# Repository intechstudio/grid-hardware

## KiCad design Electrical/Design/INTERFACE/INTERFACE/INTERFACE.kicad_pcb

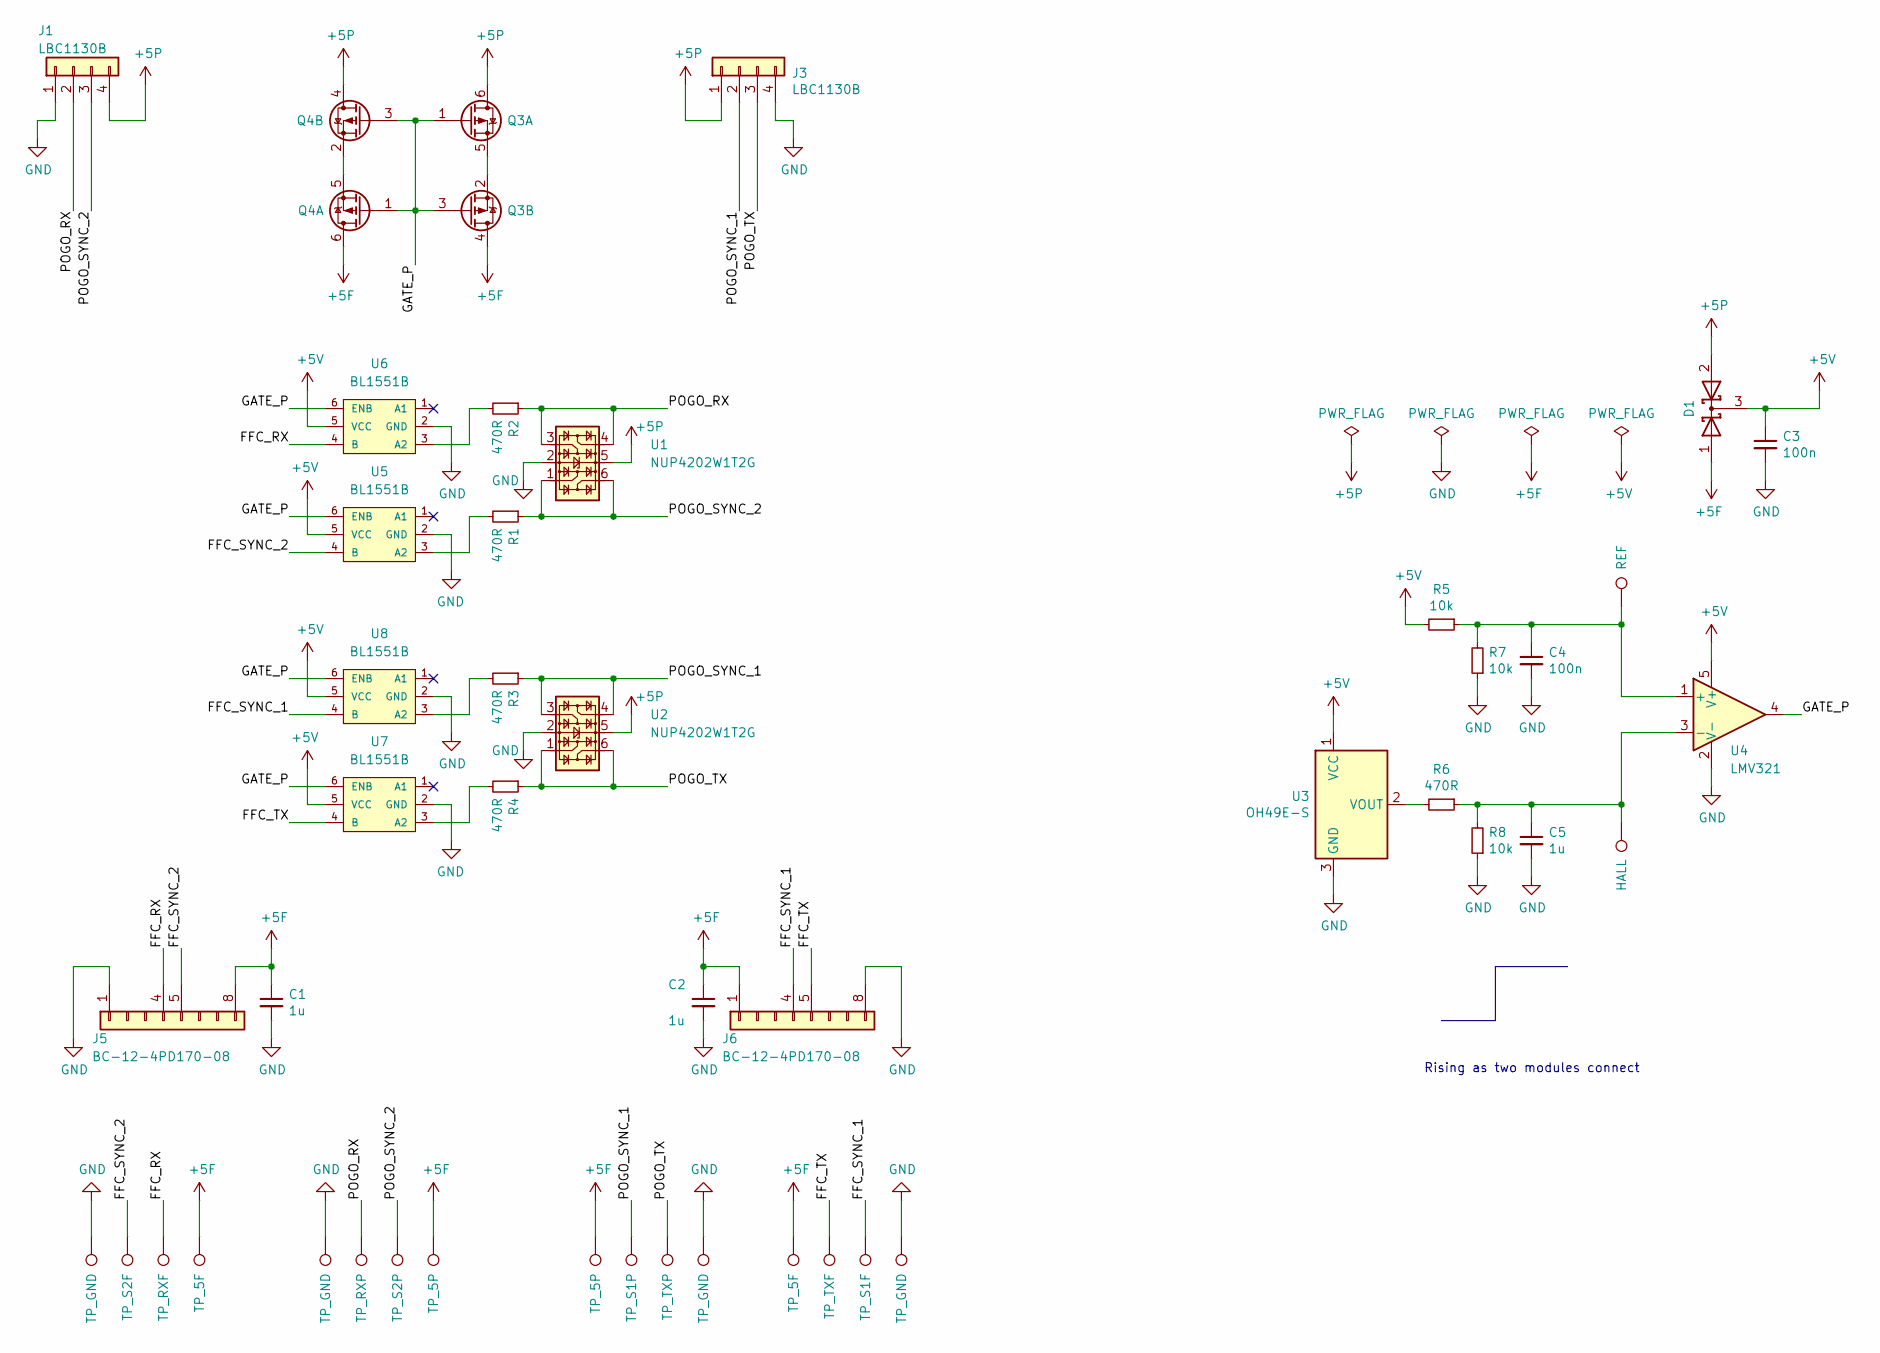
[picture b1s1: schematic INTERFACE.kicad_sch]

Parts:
C1, C2, C5: 1u; CAP_0805
C3, C4: 100n; CAP_0805
D1: BAT54C; SOT-23; Part C375703
J1, J3: LBC1130B; J_4xPOGO_SMD; Part LBC1130B
J5, J6: BC-12-4PD170-08; J_BATTERY_CONN
Q3, Q4: WST2011; SOT-23-6; Part C148368
R1, R2, R3, R4, R6: 470R; RES_0402
R5, R7, R8: 10k; RES_0805
TP1, TP8, TP9, TP16: TP_GND; TestPoint_THTPad_1.0x1.0mm_Drill0.5mm
TP2: TP_S2F; TestPoint_THTPad_1.0x1.0mm_Drill0.5mm
TP3: TP_RXF; TestPoint_THTPad_1.0x1.0mm_Drill0.5mm
TP4, TP5: TP_5F; TestPoint_THTPad_1.0x1.0mm_Drill0.5mm
TP6: TP_TXF; TestPoint_THTPad_1.0x1.0mm_Drill0.5mm
TP7: TP_S1F; TestPoint_THTPad_1.0x1.0mm_Drill0.5mm
TP10: TP_RXP; TestPoint_THTPad_1.0x1.0mm_Drill0.5mm
TP11: TP_S2P; TestPoint_THTPad_1.0x1.0mm_Drill0.5mm
TP12, TP13: TP_5P; TestPoint_THTPad_1.0x1.0mm_Drill0.5mm
TP14: TP_S1P; TestPoint_THTPad_1.0x1.0mm_Drill0.5mm
TP15: TP_TXP; TestPoint_THTPad_1.0x1.0mm_Drill0.5mm
TP17: REF; TestPoint_THTPad_1.0x1.0mm_Drill0.5mm
TP18: HALL; TestPoint_THTPad_1.0x1.0mm_Drill0.5mm
U1, U2: NUP4202W1T2G; SOT-363_SC-70-6; Part C294963
U3: OH49E-S; SOT-23W; Part C85573
U4: LMV321; SOT-23-5; Part C90297
U5, U6, U7, U8: BL1551B; SOT-363_SC-70-6

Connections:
+5F: C1.1, C2.1, D1.1 (A), J5.8, J6.1, Q3.4 (D), Q4.6 (D), TP4.1, TP5.1, TP12.1, TP13.1
+5P: D1.2 (A), J1.4, J3.1, Q3.6 (D), Q4.4 (D), U1.5, U2.5
+5V: C3.1, D1.3 (K), R5.2, U3.1 (VCC), U4.5 (V+), U5.5 (VCC), U6.5 (VCC), U7.5 (VCC), U8.5 (VCC)
/FFC_RX: J5.4, TP3.1, U6.4 (B)
/FFC_SYNC_1: J6.4, TP7.1, U8.4 (B)
/FFC_SYNC_2: J5.5, TP2.1, U5.4 (B)
/FFC_TX: J6.5, TP6.1, U7.4 (B)
/GATE_P: Q3.1 (G), Q3.3 (G), Q4.1 (G), Q4.3 (G), U4.4, U5.6 (ENB), U6.6 (ENB), U7.6 (ENB), U8.6 (ENB)
/POGO_RX: J1.2, R2.1, TP10.1, U1.3, U1.4
/POGO_SYNC_1: J3.2, R3.1, TP14.1, U2.3, U2.4
/POGO_SYNC_2: J1.3, R1.1, TP11.1, U1.1, U1.6
/POGO_TX: J3.3, R4.1, TP15.1, U2.1, U2.6
GND: C1.2, C2.2, C3.2, C4.2, C5.2, J1.1, J3.4, J5.1, J6.8, R7.1, R8.1, TP1.1, TP8.1, TP9.1, TP16.1, U1.2, U2.2, U3.3 (GND), U4.2 (V-), U5.2 (GND), U6.2 (GND), U7.2 (GND), U8.2 (GND)
unnamed: Q3.2 (S), Q3.5 (S)
unnamed: Q4.2 (S), Q4.5 (S)
unnamed: R6.2, U3.2 (VOUT)
unnamed: C4.1, R5.1, R7.2, TP17.1, U4.1 (+)
unnamed: C5.1, R6.1, R8.2, TP18.1, U4.3 (-)
unnamed: R1.2, U5.3 (A2)
unnamed: R2.2, U6.3 (A2)
unnamed: R4.2, U7.3 (A2)
unnamed: R3.2, U8.3 (A2)

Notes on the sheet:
Rising as two modules connect

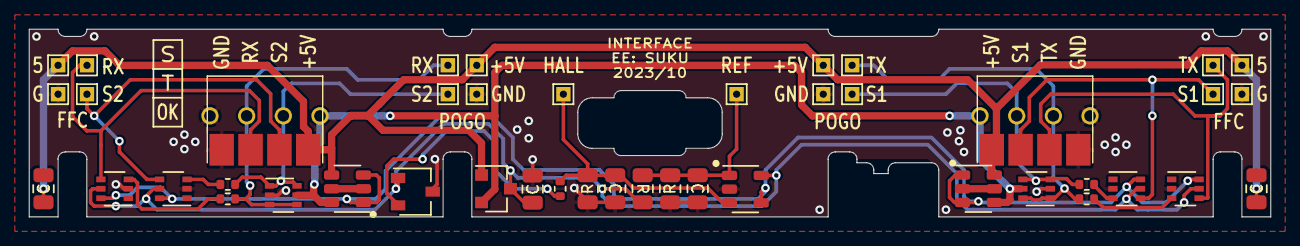
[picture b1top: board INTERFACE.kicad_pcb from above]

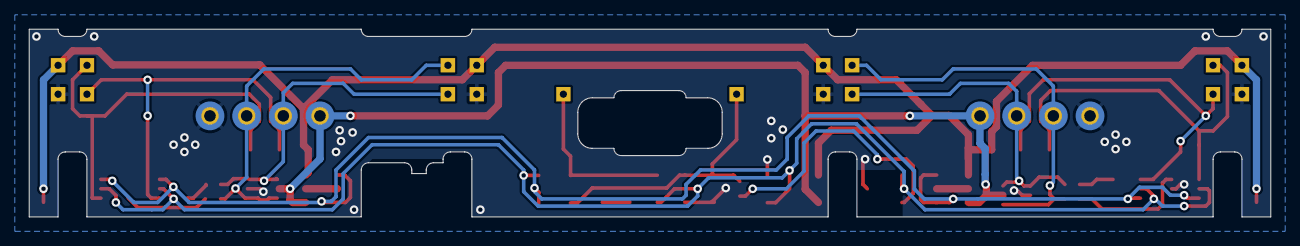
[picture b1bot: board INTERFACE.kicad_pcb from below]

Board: 2 copper layers, 86.0 x 13.0 mm, 46 parts (2 on the bottom side), 22 nets.

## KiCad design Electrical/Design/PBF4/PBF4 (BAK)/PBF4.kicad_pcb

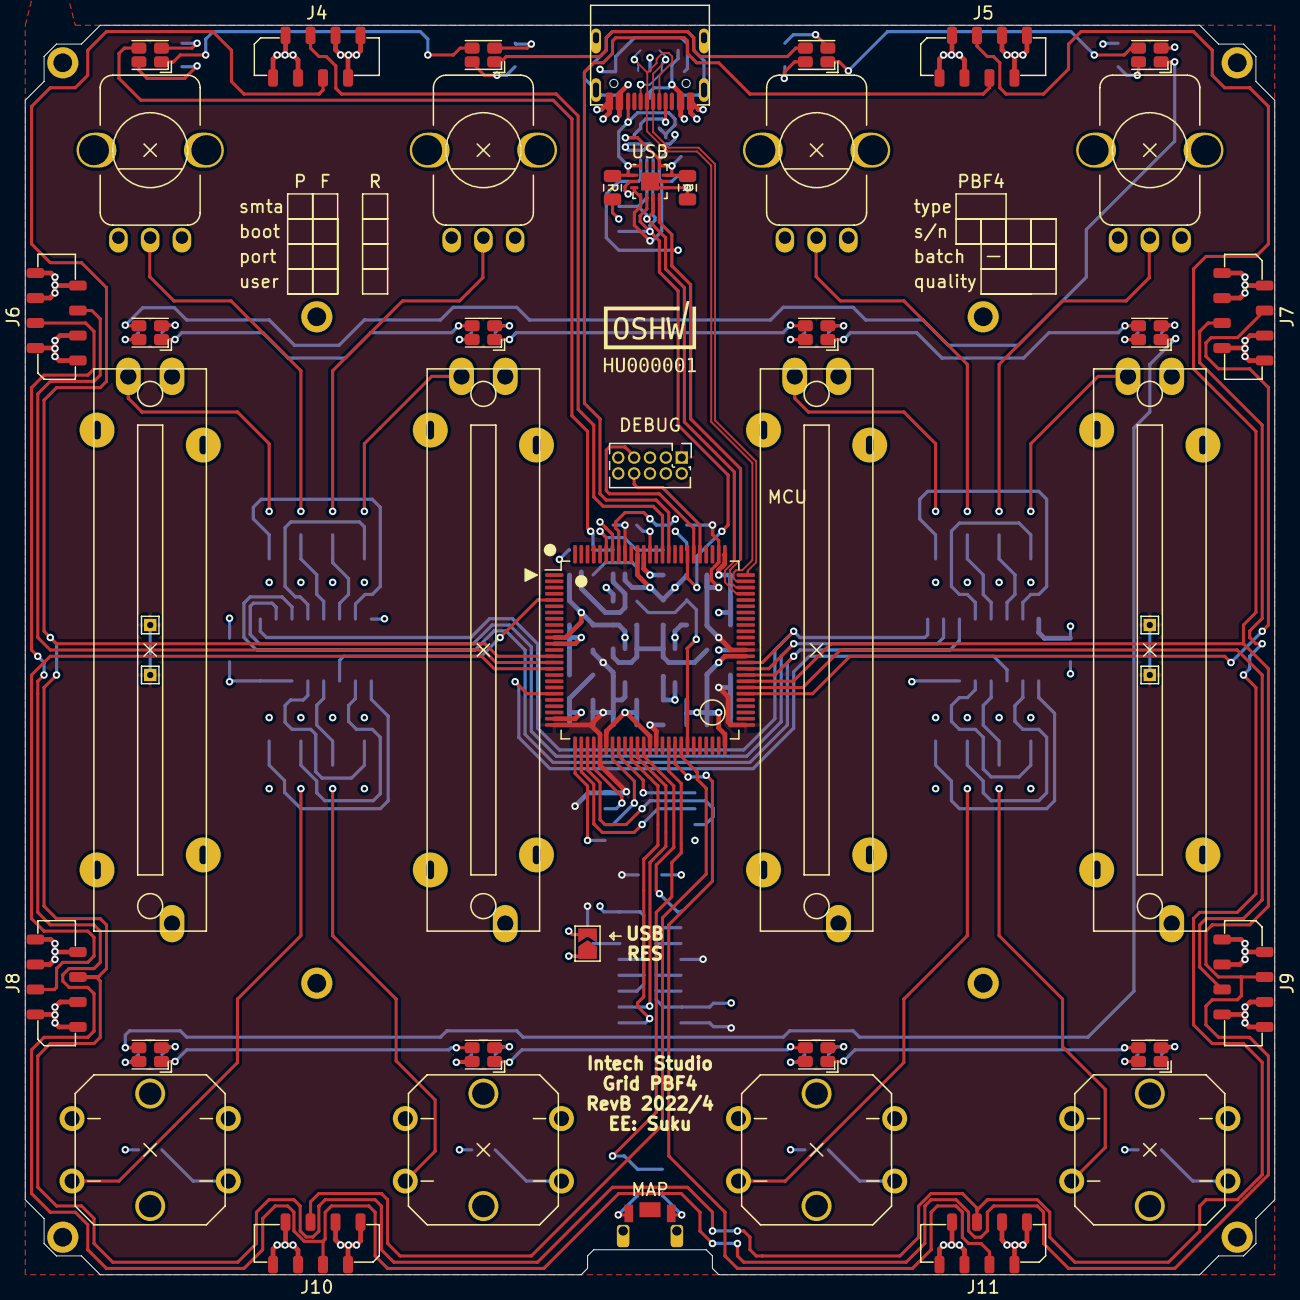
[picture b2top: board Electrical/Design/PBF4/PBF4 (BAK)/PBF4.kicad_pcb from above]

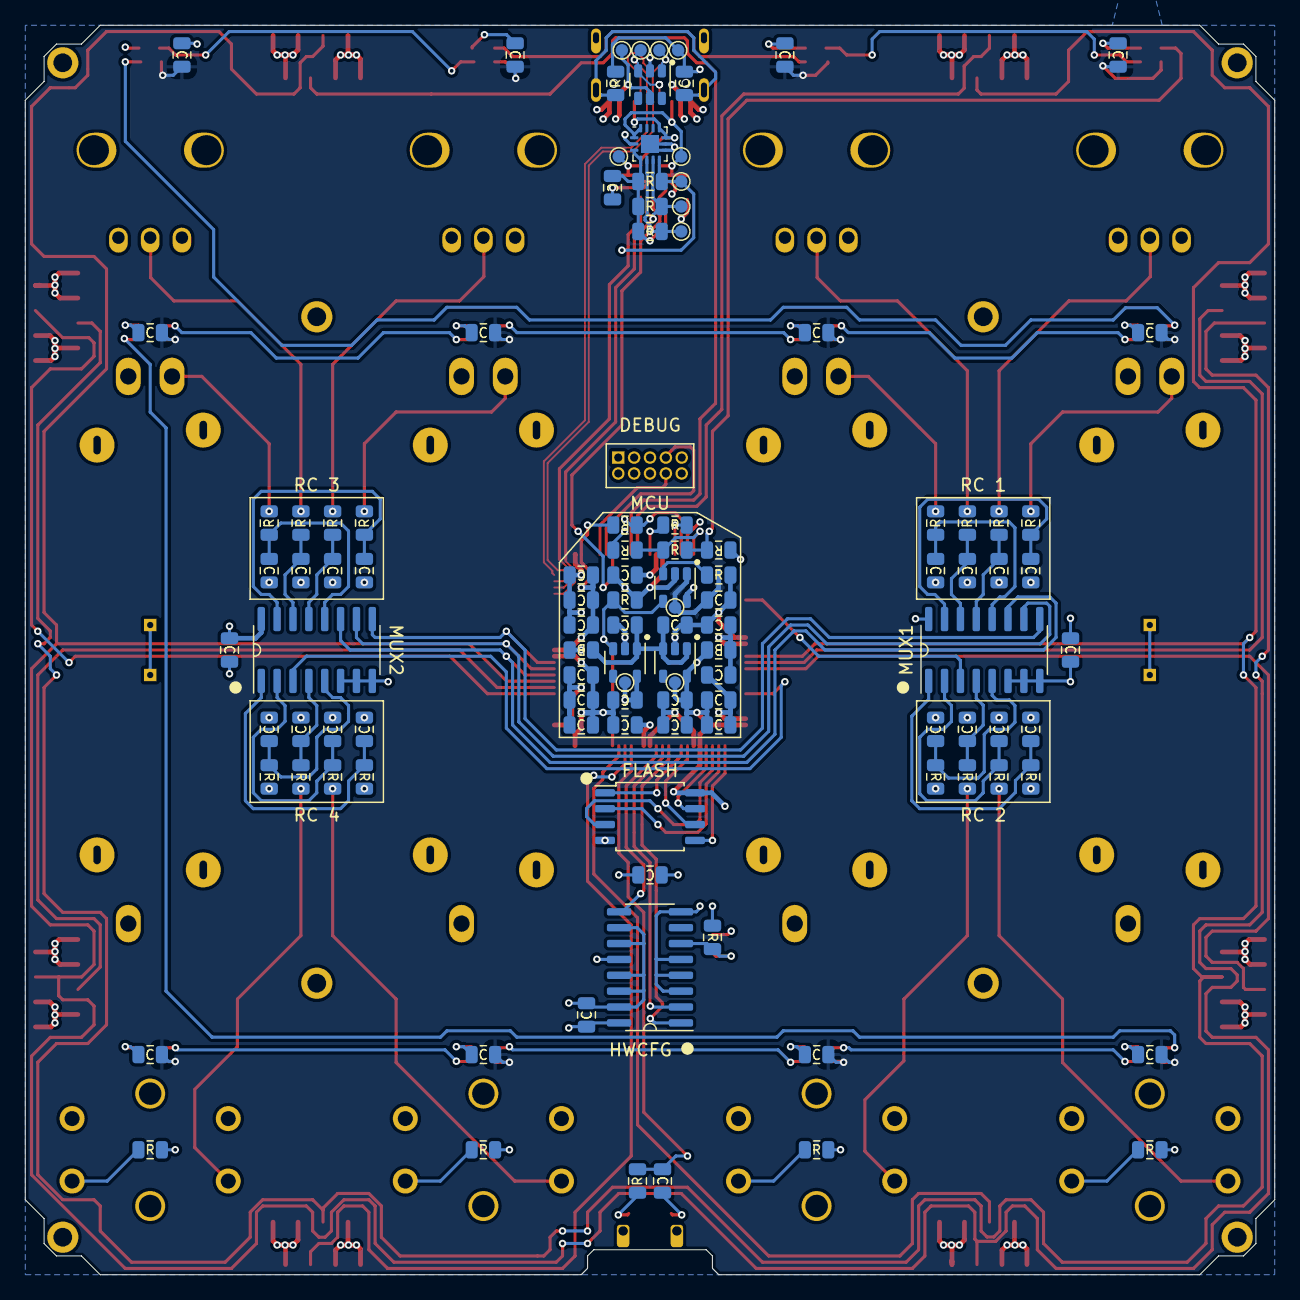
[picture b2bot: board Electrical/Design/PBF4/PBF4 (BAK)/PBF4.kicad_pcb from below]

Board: 4 copper layers, 100.0 x 100.0 mm, 155 parts (109 on the bottom side), 96 nets.

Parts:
C1, C2, C3, C4, C5, C6, C7, C8, C9, C10, C13, C14, C15, C16, C17, C18, C19, C20, C21, C22, C23, C24, C25, C26, C27, C28, C29, C30, C31, C32, C33, C35, C39, C41, C42, C44, C45, C46, C47, C48, C49, C50, C52, C54, C55: 100n; CAP_0805
C11, C12, C34, C36, C40: 1u; CAP_0805
C37: 4n7; CAP_0805
C38, C43: 10u; CAP_0805
D1, D2, D3, D4, D5, D6, D7, D8, D13, D14, D15, D16: WS2812C-2020; UI_WS2812C-2020
J1: USB_C_TYPE-C-32-M-12; USB_C_Korean_Hroparts_TYPE-C-31-M-12
J2: (NF); PinHeader_2x05_P1.27mm_Vertical
J4, J5, J6, J7, J8, J9, J10, J11: TE Connectivity 84982-8; grid_ffc_8_vertical_smd
JP1: (NF); SolderJumper-2_P1.3mm_Open_TrianglePad1.0x1.5mm
L1, L2: GZ2012D601TF; FERRIT_0805
LOGO1: OSHWA
M1: (NF); grid_outline
R1, R2, R3, R4, R6, R7: 5k1; RES_0805
R5, R8, R10, R13, R14, R15, R16: 10k; RES_0805
R9: 1M; RES_0805
R17, R18, R19, R20, R21, R22, R23, R24, R25, R26, R27, R28, R29, R30, R31, R32, R38, R39, R40, R41, R42: 1k; RES_0805
SW1: C255807; SW_HYP_MAPMODE
TP1, TP2, TP3, TP4: TestPoint; TestPoint_THTPad_1.0x1.0mm_Drill0.5mm
TP9: GND; TestPoint_Pad_D1.0mm
TP10: VB; TestPoint_Pad_D1.0mm
TP11: D-; TestPoint_Pad_D1.0mm
TP12: D+; TestPoint_Pad_D1.0mm
TP13: UC; TestPoint_Pad_D1.0mm
TP14: SDA; TestPoint_Pad_D1.0mm
TP15: SCL; TestPoint_Pad_D1.0mm
TP16: INT; TestPoint_Pad_D1.0mm
TP17: UI; TestPoint_Pad_D1.0mm
TP18: UI_5V; TestPoint_Pad_D1.0mm
TP19: CC1; TestPoint_Pad_D1.0mm
TP20: CC2; TestPoint_Pad_D1.0mm
U1, U2: 74HC4051; SOIC-16_74HC4051
U3: 74HC165; SOIC-16_74HC165
U4: SESRV05-4; SOT-23-6
U5, U9: LN1134A332MR-G; SOT-23-5
U6, U10: FUSB302BMPX (NF); WQFN-14-1EP_2.5x2.5mm_P0.5mm_EP1.45x1.45mm
U7: SAMD51N20A; TQFP-100_14x14mm_P0.5mm
U8: W25Q16JVSSIQ; SOIC-8W_FLASH
U11: MT9700; SOT-23-5
UI1, UI2, UI3, UI4: P090S-04F20BR10K (NF); UI_POT_TT
UI5, UI6, UI7, UI8: PS30-10MC1BR10K (NF); UI_FADER_TT
UI29, UI30, UI31, UI32: B3F-4050 (NF); UI_BUTTON_OMRON

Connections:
+3V3_UC: C9.1, C33.1, C40.1, C41.1, C42.1, C43.1, C44.1, C45.1, C46.1, C47.1, C48.1, C50.1, C54.1, C55.1, J2.1, L1.2, R2.1, R3.1, R4.1, R10.1, R38.2, R39.2, TP1.1, TP2.1, TP3.1, TP4.1, TP13.1, U3.12 (D1), U3.16 (VCC), U5.5 (OUT), U6.3 (VDD), U6.4 (VDD), U7.25 (VDDIOB0), U7.30 (VDDIOB1), U7.39 (VDDIO0), U7.51 (VDDIO1), U7.63 (VDDIO2), U7.77 (VDDIO3), U7.92 (VDDIO4), U8.8 (VCC), U10.3 (VDD), U10.4 (VDD)
+3V3_UI: C12.1, C35.1, C52.1, R13.2, R14.2, R15.2, R16.2, TP17.1, U1.16 (VDD), U2.16 (VDD), U9.5 (OUT), UI1.1, UI2.1, UI3.1, UI4.1, UI5.1, UI6.1, UI7.1, UI8.1
+5V: J1.A4B9 (VBUS), J1.A9B4 (VBUS), J4.1, J4.2, J4.3, J5.6, J5.7, J5.8, J6.6, J6.7, J6.8, J7.1, J7.2, J7.3, J8.1, J8.2, J8.3, J9.6, J9.7, J9.8, J10.6, J10.7, J10.8, J11.1, J11.2, J11.3, L2.2, R1.1, TP10.1, U4.5, U6.2 (VBUS), U10.2 (VBUS), U11.5 (IN)
+5V_UI: C1.2, C2.2, C3.2, C4.2, C5.2, C6.2, C7.2, C8.2, C13.2, C14.2, C15.2, C16.2, C36.1, D1.4 (VDD), D2.4 (VDD), D3.4 (VDD), D4.4 (VDD), D5.4 (VDD), D6.4 (VDD), D7.4 (VDD), D8.4 (VDD), D13.4 (VDD), D14.4 (VDD), D15.4 (VDD), D16.4 (VDD), TP18.1, U11.1 (OUT)
/ANA_0: R17.2, UI1.2
/ANA_1: R18.2, UI2.2
/ANA_2: R25.2, UI3.2
/ANA_3: R26.2, UI4.2
/ANA_4: R19.2, UI5.2
/ANA_5: R20.2, UI6.2
/ANA_6: R27.2, UI7.2
/ANA_7: R28.2, UI8.2
/ANA_12: R23.2, UI29.3
/ANA_13: R24.2, UI30.3
/ANA_14: R31.2, UI31.3
/ANA_15: R32.2, UI32.3
/HWCFG/HWCFG_CLOCK: U3.2 (CLK), U7.36 (PB14)
/HWCFG/HWCFG_DATA: U3.9 (Q), U7.37 (PB15)
/HWCFG/HWCFG_SHIFT: U3.1 (SH/~LD), U7.35 (PB13)
/MCU/GRID_AUX_RX: J2.8, U7.80 (PB24)
/MCU/GRID_AUX_TX: J2.7, U7.81 (PB25)
/MCU/GRID_EAST_RX: J7.4, U7.56 (PC16)
/MCU/GRID_EAST_TX: J9.5, U7.57 (PC17)
/MCU/GRID_NORTH_RX: J4.4, U7.86 (PC28)
/MCU/GRID_NORTH_TX: J5.5, U7.85 (PC27)
/MCU/GRID_SOUTH_RX: J11.4, U7.42 (PC12)
/MCU/GRID_SOUTH_TX: J10.5, U7.43 (PC13)
/MCU/GRID_SYNC_1: J5.4, J6.4, J9.4, J10.4, U7.58 (PC18)
/MCU/GRID_SYNC_2: J4.5, J7.5, J8.5, J11.5, U7.14 (PB07)
/MCU/GRID_WEST_RX: J8.4, U7.16 (PB09)
/MCU/GRID_WEST_TX: J6.5, U7.15 (PB08~)
/MCU/LED_DATA_OUT: D1.3 (DIN), R1.2, R42.2
/MCU/MAP_MODE: C10.1, R40.2, U7.41 (PC11)
/MCU/MUX_ADDRESS_A: U1.11 (A), U2.11 (A), U7.59 (PC19)
/MCU/MUX_ADDRESS_B: U1.10 (B), U2.10 (B), U7.60 (PC20)
/MCU/MUX_ADDRESS_C: U1.9 (C), U2.9 (C), U7.61 (PC21)
/MCU/MUX_OUT_1: U1.3 (X), U7.5 (PC02)
/MCU/MUX_OUT_2: U2.3 (X), U7.20 (PA07)
/MCU/QSPI_IO_0: U7.26 (PA08), U8.5 (DI(IO0))
/MCU/QSPI_IO_1: U7.27 (PA09), U8.2 (DO(IO1))
/MCU/QSPI_IO_2: U7.28 (PA10), U8.3 (IO2)
/MCU/QSPI_IO_3: U7.29 (PA11), U8.7 (IO3)
/MCU/QSPI_SCK: U7.32 (PB10), U8.6 (CLK)
/MCU/QSPI_~CE: U7.33 (PB11), U8.1 (~CS)
/MCU/SYS_I2C_INT_0: R4.2, TP16.1, U6.5 (INT_N), U7.82 (PC24), U10.5 (INT_N)
/MCU/SYS_I2C_SCL: R3.2, TP15.1, U6.6 (SCL), U7.72 (PA22), U10.6 (SCL)
/MCU/SYS_I2C_SDA: R2.2, TP14.1, U6.7 (SDA), U7.73 (PA23), U10.7 (SDA)
/MCU/SYS_RESET: J2.10, R38.1, U7.88 (~RESET)
/MCU/SYS_SWCLK: J2.4, R39.1, U7.93 (PA30)
/MCU/SYS_SWDIO: J2.2, U7.94 (PA31)
/MCU/SYS_SWO: J2.6, R41.2
/MCU/Sheet60F06FE1/USB_CC1: J1.A5 (CC1), R6.1, TP19.1, U6.10 (CC1), U6.11 (CC1), U10.10 (CC1), U10.11 (CC1)
/MCU/Sheet60F06FE1/USB_CC2: J1.B5 (CC2), R7.1, TP20.1, U6.1 (CC2), U6.14 (CC2), U10.1 (CC2), U10.14 (CC2)
/MCU/UI_PWR_EN: R5.1, U7.44 (PC14), U9.3 (EN), U11.4 (ON)
/MCU/USB_DN: J1.A7 (D-), J1.B7 (D-), TP11.1, U4.1, U7.74 (PA24)
/MCU/USB_DP: J1.A6 (D+), J1.B6 (D+), TP12.1, U4.3, U7.75 (PA25)
GND: C1.1, C2.1, C3.1, C4.1, C5.1, C6.1, C7.1, C8.1, C9.2, C10.2, C11.2, C12.2, C13.1, C14.1, C15.1, C16.1, C17.2, C18.2, C19.2, C20.2, C21.2, C22.2, C23.2, C24.2, C25.2, C26.2, C27.2, C28.2, C29.2, C30.2, C31.2, C32.2, C33.2, C34.2, C35.2, C36.2, C37.2, C38.2, C39.2, C40.2, C41.2, C42.2, C43.2, C44.2, C45.2, C46.2, C47.2, C48.2, C49.2, C50.2, C52.2, C54.2, C55.2, D1.2 (VSS), D2.2 (VSS), D3.2 (VSS), D4.2 (VSS), D5.2 (VSS), D6.2 (VSS), D7.2 (VSS), D8.2 (VSS), D13.2 (VSS), D14.2 (VSS), D15.2 (VSS), D16.2 (VSS), J1.A1B12 (GND), J1.A12B1 (GND), J2.3, J2.5, J2.9, J4.6, J4.7, J4.8, J5.1, J5.2, J5.3, J6.1, J6.2, J6.3, J7.6, J7.7, J7.8, J8.6, J8.7, J8.8, J9.1, J9.2, J9.3, J10.1, J10.2, J10.3, J11.6, J11.7, J11.8, JP1.2 (B), R5.2, R6.2, R7.2, R8.2, R9.2, R21.2, R22.2, R29.2, R30.2, SW1.2 (B), TP9.1, U1.6 (Inh), U1.7 (VEE), U1.8 (VSS), U2.6 (Inh), U2.7 (VEE), U2.8 (VSS), U3.3 (D4), U3.4 (D5), U3.5 (D6), U3.8 (GND), U3.10 (SI), U3.11 (D0), U3.13 (D2), U3.14 (D3), U3.15 (INH), U4.2, U5.2 (GND), U6.8 (GND), U6.9 (GND), U6.15 (GND), U7.11 (GNDANA), U7.24 (GNDIOB0), U7.31 (GNDIOB0), U7.38 (GND0), U7.50 (GND1), U7.62 (GND2), U7.76 (GND3), U7.90 (GND4), U8.4 (GND), U9.2 (GND), U10.8 (GND), U10.9 (GND), U10.15 (GND), U11.2 (GND), UI1.3, UI2.3, UI3.3, UI4.3, UI5.3, UI6.3, UI7.3, UI8.3, UI29.1, UI29.2, UI30.1, UI30.2, UI31.1, UI31.2, UI32.1, UI32.2
unnamed: C11.1, C34.1, L2.1, U5.1 (IN), U5.3 (EN), U9.1 (IN)
unnamed: C17.1, R17.1, U1.13 (X0)
unnamed: C18.1, R18.1, U1.14 (X1)
unnamed: C19.1, R19.1, U1.15 (X2)
unnamed: C20.1, R20.1, U1.12 (X3)
unnamed: C21.1, R21.1, U1.1 (X4)
unnamed: C22.1, R22.1, U1.5 (X5)
unnamed: C23.1, R23.1, U1.2 (X6)
unnamed: C24.1, R24.1, U1.4 (X7)
unnamed: C25.1, R25.1, U2.13 (X0)
unnamed: C26.1, R26.1, U2.14 (X1)
unnamed: C27.1, R27.1, U2.15 (X2)
unnamed: C28.1, R28.1, U2.12 (X3)
unnamed: C29.1, R29.1, U2.1 (X4)
unnamed: C30.1, R30.1, U2.5 (X5)
unnamed: C31.1, R31.1, U2.2 (X6)
unnamed: C32.1, R32.1, U2.4 (X7)
unnamed: C37.1, J1.S1 (SHIELD), J1.S2 (SHIELD), R9.1
unnamed: C38.1, C39.1, L1.1, U7.12 (VDDANA)
unnamed: C49.1, U7.89 (VDDCORE)
unnamed: D1.1 (DOUT), D2.3 (DIN)
unnamed: D2.1 (DOUT), D3.3 (DIN)
unnamed: D3.1 (DOUT), D4.3 (DIN)
unnamed: D4.1 (DOUT), D5.3 (DIN)
unnamed: D5.1 (DOUT), D6.3 (DIN)
unnamed: D6.1 (DOUT), D7.3 (DIN)
unnamed: D7.1 (DOUT), D8.3 (DIN)
unnamed: D13.1 (DOUT), D14.3 (DIN)
unnamed: D8.1 (DOUT), D13.3 (DIN)
unnamed: D14.1 (DOUT), D15.3 (DIN)
unnamed: D15.1 (DOUT), D16.3 (DIN)
unnamed: JP1.1 (A), R10.2, U3.6 (D7)
unnamed: R8.1, U11.3 (SET)
unnamed: R13.1, UI29.4
unnamed: R14.1, UI30.4
unnamed: R15.1, UI31.4
unnamed: R16.1, UI32.4
unnamed: R40.1, SW1.1 (A)
unnamed: R41.1, R42.1, U7.95 (PB30)

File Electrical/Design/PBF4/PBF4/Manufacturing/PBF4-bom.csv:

Id,Designator,Footprint,Quantity,Comment
1,U8,SOIC-8_WIDE(rot90),1,W25Q16JVSSIQ
2,U3,SOIC-16_3.9x9.9mm_P1.27mm(rot90),1,74HC165
3,"UI5,UI8,UI7,UI6",UI_FADER_TT,4,UI_Fader
4,SW1,SW_HYP_MAPMODE,1,SW_SPST
5,"C1,C16,C8,C4,C15,C7,C3,C14,C6,C2,C13,C5,C55,C54,C44,C49,C48,C47,C46,C45,C42,C41,C39,C52,C35,C9,C33,C32,C30,C28,C26,C31,C29,C27,C25,C24,C22,C20,C18,C23,C21,C19,C17,C10",CAP_0805,44,100n
6,"D16,D8,D4,D15,D7,D3,D14,D6,D2,D13,D5,D1",UI_WS2812C-2020,12,UI_WS2812C-2020
7,M1,grid_outline,1,Conn_01x08
8,Y1,Crystal_SMD_3215-2Pin_3.2x1.5mm,1,N.F.16Mhz
9,U4,SOT-23-6,1,SESRV05-4
10,J1,USB_C_Korean_Hroparts,1,TYPE-C-31-M-04
11,R37,RES_0805,1,1M
12,"U2,U1",SOIC-16_3.9x9.9mm_P1.27mm,2,74HC4051
13,"U6,U5",SOT-23-5,2,LN1134A332MR-G
14,U7,TQFP-100_14x14mm_P0.5mm,1,SAMD51N20A
15,"TP4,TP3,TP2,TP1",TestPoint_THTPad_1.0x1.0mm_Drill0.5mm,4,TestPoint
16,"C53,C36,C40,C34",CAP_0805,4,1u
17,"C50,C51",CAP_0805,2,N.F.18p
18,"R36,R16,R15,R14,R13",RES_0805,5,10k
19,"FB2,FB1",FERRIT_0805,2,600 Ohm @ 100MHz
20,"C43,C38",CAP_0805,2,10u
21,"J11,J10,J9,J7,J5,J4,J8,J6",grid_ffc_8_vertical,8,Conn_01x08
22,"UI32,UI31,UI30,UI29",UI_BUTTON_OMRON,4,UI_Pushbutton_Omron
23,"UI4,UI3,UI2,UI1",UI_POT_TT,4,UI_Potentiometer
24,"R39,R38,R40,R42,R41,R32,R30,R28,R26,R31,R29,R27,R25,R24,R22,R20,R18,R23,R21,R19,R17",RES_0805,21,1k
25,"R35,R34",RES_0805,2,5k1
26,J2,PinHeader_2x05_P1.27mm_Vertical,1,N.F.
27,J3,PinHeader_1x03_P2.54mm_Vertical,1,N.F.
28,C37,CAP_0805,1,4n7

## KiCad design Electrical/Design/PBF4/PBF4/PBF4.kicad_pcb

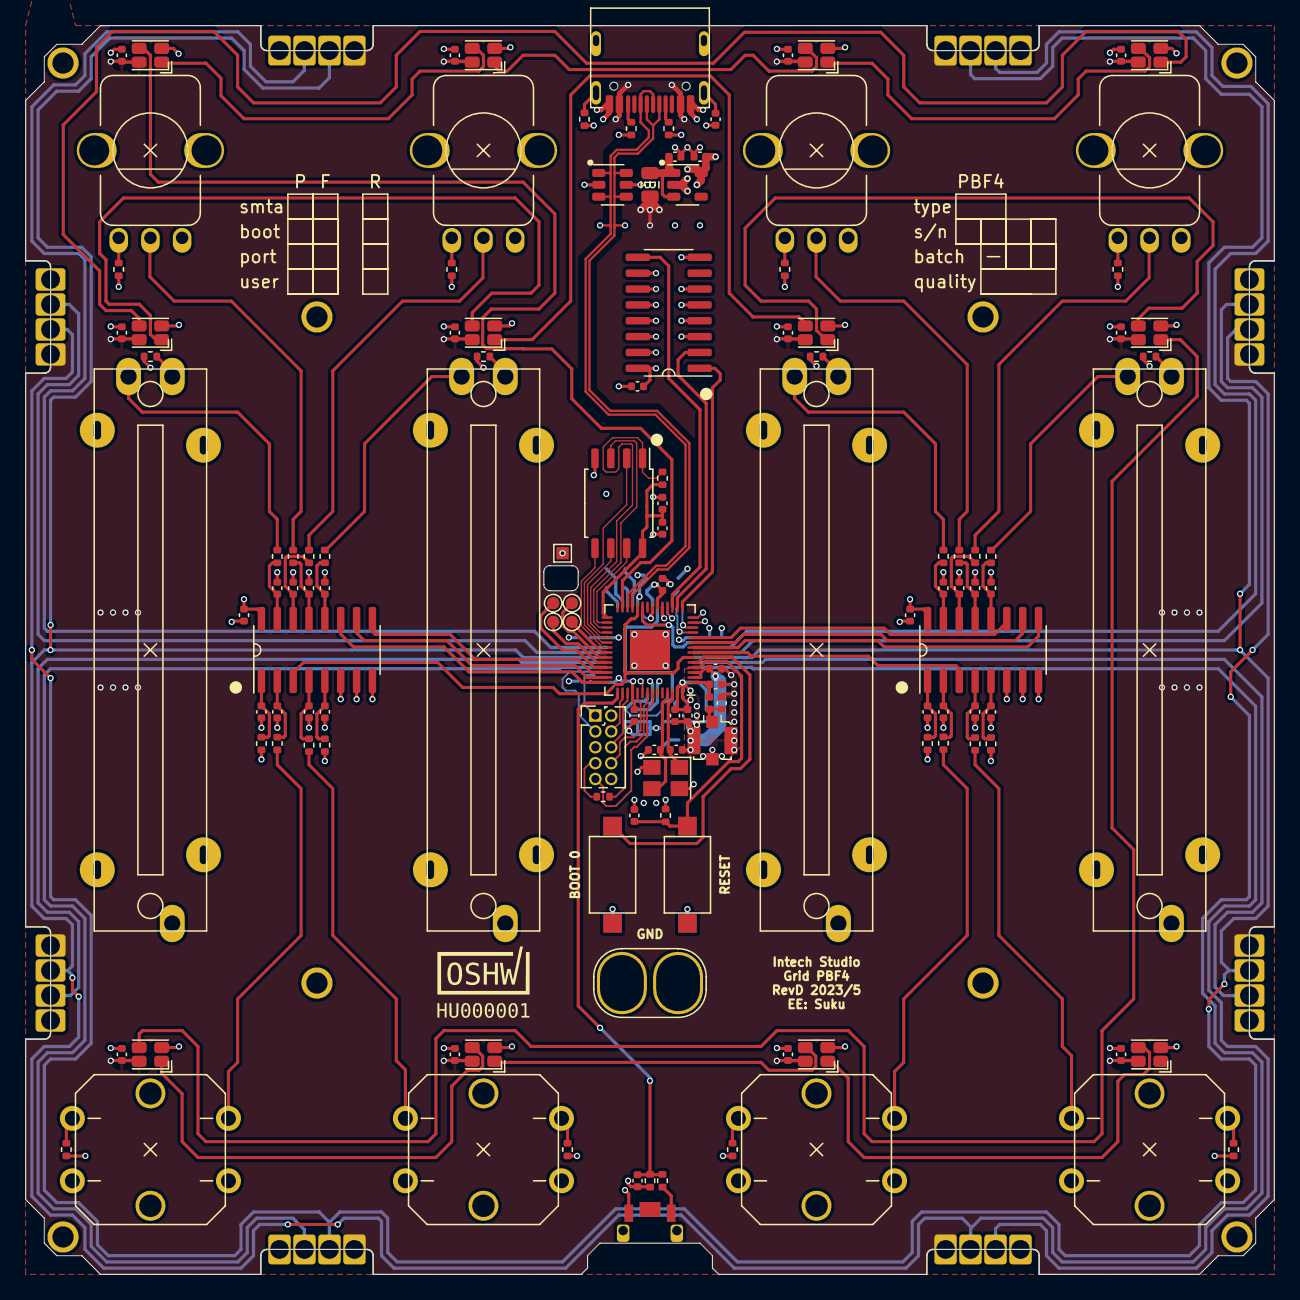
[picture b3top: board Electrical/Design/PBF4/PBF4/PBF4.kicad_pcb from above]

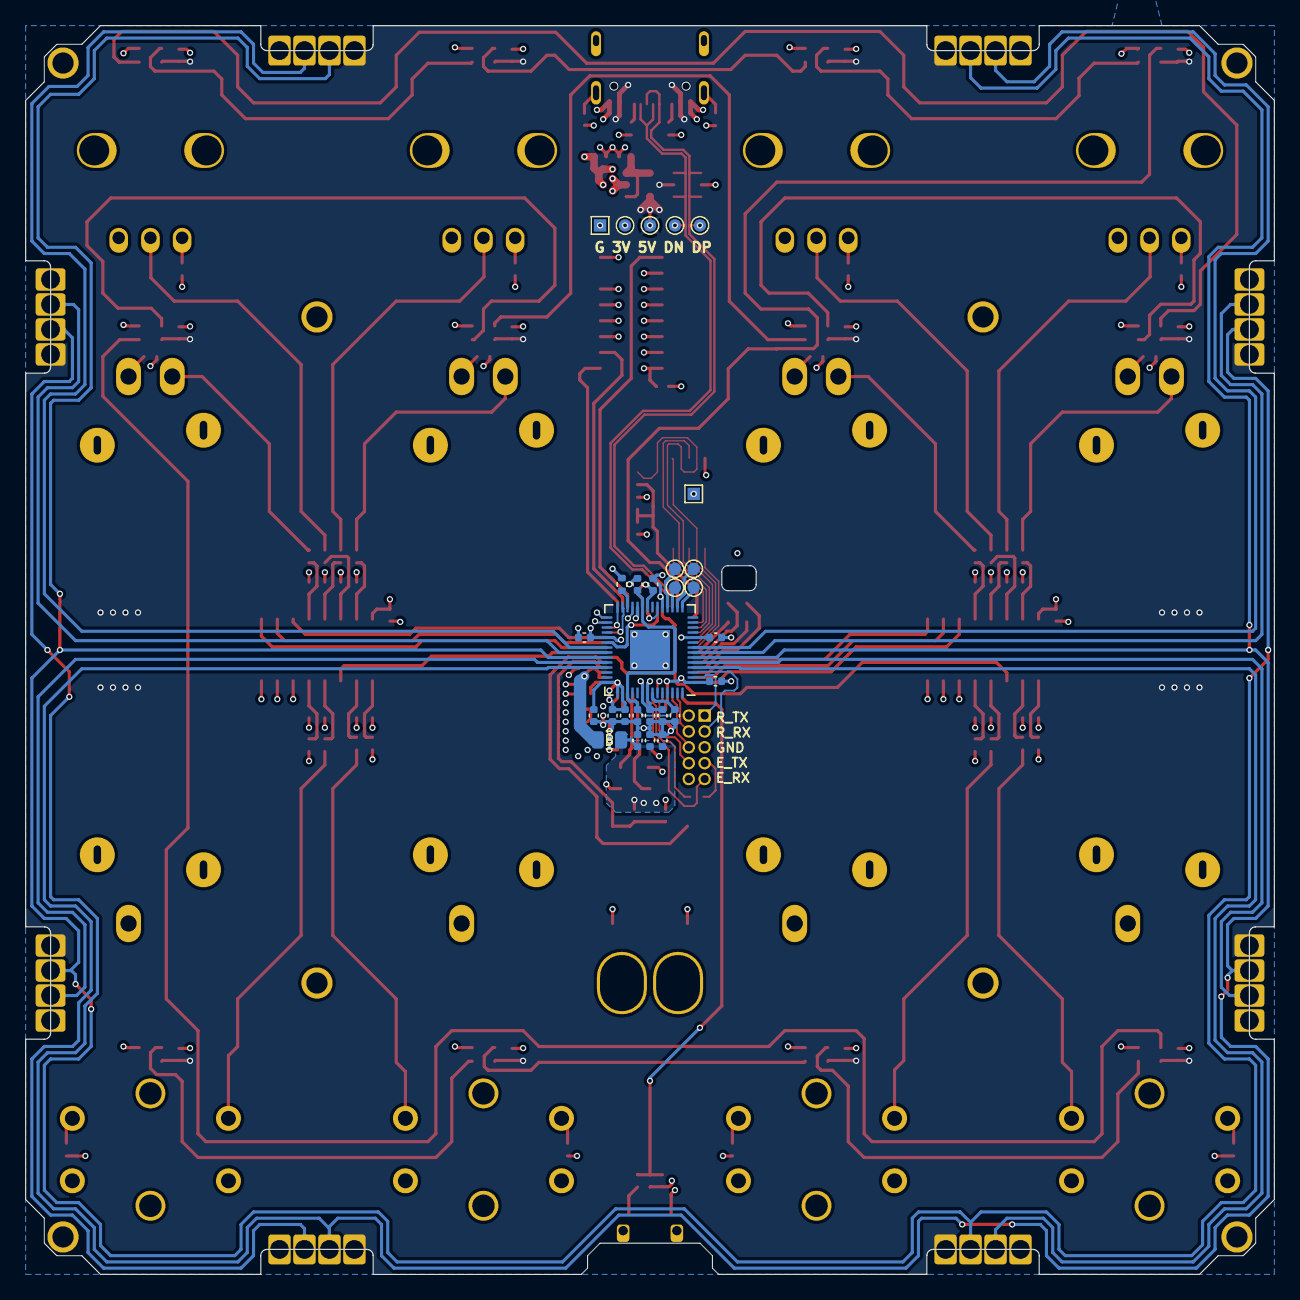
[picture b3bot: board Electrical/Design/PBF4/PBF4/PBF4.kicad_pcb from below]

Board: 4 copper layers, 100.0 x 100.0 mm, 167 parts (28 on the bottom side), 126 nets.

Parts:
C731, C732, C735, C736, C737, C738, C740, C741, C744, C745, C747, C749, C751, C752, C756, C757, C801, C901, C902, C903, C904, C905, C906, C907, C908, C909, C910, C911, C912, C1001, C1002, C1003, C1004, C1005, C1006, C1007, C1008, C1009, C1010, C1011, C1012, C1013, C1014, C1015, C1016, C1017, C1018: 100n; CAP_0402
C733, C734, C746, C754, C755, C758, C760, C761: 1u; CAP_0402
C739: 3p9; CAP_0402
C742: 1p8; CAP_0402
C743: 10u; CAP_0402
C748, C750: 10p; CAP_0402
C753: 10n; CAP_0402
C759: 4n7; CAP_0402
D901, D902, D903, D904, D905, D906, D907, D908, D909, D910, D911, D912: WS2812C-2020; UI_WS2812C-2020
J701: Conn_Coaxial; U.FL_Molex_MCRF_73412-0110_Vertical
J702: (NF); PinHeader_2x05_P1.27mm_Vertical
J703, J704, J705, J706, J707, J708, J709, J710: AFB10-S08LCA-00; J_INTERFACE_SPRINGPATTERN
J711: USB_C_TYPE-C-32-M-12; USB_C_Korean_Hroparts_TYPE-C-31-M-12
J799: Conn_01x02; OscilloscopeGround
L701: 1n8; IND_0402
L702, L703: GZ2012D601TF; FERRIT_0805
LOGO701: LOGO; OSHWA
M701: (NF); grid_outline
R701, R729, R734, R735, R738, R739: 5k1; RES_0402
R733, R736, R1001, R1002, R1003, R1004, R1005, R1006, R1007, R1008, R1009, R1010, R1011, R1012, R1013, R1014, R1015, R1016: 1k; RES_0402
R737: 1M; RES_0402
R1017, R1018, R1019, R1020, R1021, R1022, R1023, R1024: 470R; RES_0402
R1025, R1026, R1027, R1028: 10k; RES_0402
SW701: C255807; SW_HYP_MAPMODE
SW702, SW703: C2905169; SW_SPST_CK_RS282G05A3
TP701, TP702, TP703, TP704, TP706, TP707, TP708, TP709: TestPoint; TestPoint_Pad_D1.0mm
TP705, TP710: TestPoint; TestPoint_Pad_1.0x1.0mm
TP711: GND; TestPoint_Pad_1.0x1.0mm
TP712: VB; TestPoint_Pad_D1.0mm
TP713: D-; TestPoint_Pad_D1.0mm
TP714: D+; TestPoint_Pad_D1.0mm
TP715: UI; TestPoint_Pad_D1.0mm
U703: RP2040; RP2040_QFN-56-1EP_7x7mm_P0.4mm_EP3.2x3.2mm
U704: ESP32-S3FN8; QFN-56-1EP_7x7mm_P0.4mm_EP3.2x3.2mm
U705: W25Q64JVSSIQ; SOIC-8W_FLASH
U706: SESRV05-4; SOT-23-6
U707: LN1134A332MR-G; SOT-23-5
U801: 74HC165; SOIC-16_74HC165
U1001, U1002: 74HC4051; SOIC-16_74HC4051
UI1001, UI1003, UI1005, UI1007: P090S-04F20BR10K (NF); UI_POT_TT
UI1002, UI1004, UI1006, UI1008: PS30-10MC1BR10K (NF); UI_FADER_TT
UI1009, UI1010, UI1011, UI1012: B3F-4050 (NF); UI_BUTTON_OMRON
Y701: ESP32_XTAL; Crystal_SMD_Abracon_ABM8G-4Pin_3.2x2.5mm

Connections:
+1V1: C731.1, C732.1, C733.1, U703.23 (DVDD), U703.45 (VREG_VOUT), U703.50 (DVDD)
+3V3: C734.1, C735.1, C736.1, C737.1, C738.1, C740.1, C741.1, C743.1, C744.1, C745.1, C746.1, C747.1, C751.1, C752.1, C753.1, C754.1, C757.2, C761.2, C801.1, C1009.1, C1018.1, L702.2, R701.1, R729.1, R735.1, R1017.1, R1018.1, R1019.1, R1020.1, R1021.1, R1022.1, R1023.1, R1024.1, R1025.2, R1026.2, R1027.2, R1028.2, TP715.1, U703.1 (IOVDD), U703.10 (IOVDD), U703.22 (IOVDD), U703.33 (IOVDD), U703.42 (IOVDD), U703.43 (ADC_AVDD), U703.44 (VREG_IN), U703.48 (USB_VDD), U703.49 (IOVDD), U704.20 (VDD3P3_RTC), U704.46 (VDD3P3_CPU), U704.55 (VDDA1), U704.56 (VDDA2), U707.5 (OUT), U801.6 (D7), U801.12 (D1), U801.16 (VCC), U1001.16 (VDD), U1002.16 (VDD)
+5V: C901.2, C902.2, C903.2, C904.2, C905.2, C906.2, C907.2, C908.2, C909.2, C910.2, C911.2, C912.2, D901.4 (VDD), D902.4 (VDD), D903.4 (VDD), D904.4 (VDD), D905.4 (VDD), D906.4 (VDD), D907.4 (VDD), D908.4 (VDD), D909.4 (VDD), D910.4 (VDD), D911.4 (VDD), D912.4 (VDD), J703.4, J704.1, J705.1, J706.4, J707.4, J708.1, J709.1, J710.4, J711.A4B9 (VBUS), J711.A9B4 (VBUS), L703.2, TP712.1, U706.5
/ANA_0: R1001.2, UI1001.2
/ANA_1: R1005.2, UI1003.2
/ANA_2: R1009.2, UI1005.2
/ANA_3: R1013.2, UI1007.2
/ANA_4: R1002.2, UI1002.2
/ANA_5: R1006.2, UI1004.2
/ANA_6: R1010.2, UI1006.2
/ANA_7: R1014.2, UI1008.2
/ANA_12: R1004.2, UI1009.3
/ANA_13: R1008.2, UI1010.4
/ANA_14: R1012.2, UI1011.3
/ANA_15: R1016.2, UI1012.4
/HWCFG/HWCFG_CLOCK: U704.16 (GPIO11), U801.2 (CLK)
/HWCFG/HWCFG_DATA: U704.17 (GPIO12), U801.9 (Q)
/HWCFG/HWCFG_SHIFT: U704.15 (GPIO10), U801.1 (SH/~LD)
/MCU/ESP_BOOT0: SW703.2 (B), U704.5 (GPIO0)
/MCU/ESP_LNA: C742.1, L701.2, U704.1 (LNA_IN)
/MCU/ESP_RESET: C758.1, R735.2, SW702.2 (B), U704.4 (CHIP_PU)
/MCU/GRID_EAST_RX: J709.3, U703.36 (GPIO24)
/MCU/GRID_EAST_TX: J710.2, U703.38 (GPIO26_ADC0)
/MCU/GRID_NORTH_RX: J705.3, U703.8 (GPIO6)
/MCU/GRID_NORTH_TX: J707.2, U703.35 (GPIO23)
/MCU/GRID_SOUTH_RX: J708.3, U703.39 (GPIO27_ADC1)
/MCU/GRID_SOUTH_TX: J706.2, U703.4 (GPIO2)
/MCU/GRID_SYNC_1: J703.3, J706.3, J707.3, J710.3, U703.37 (GPIO25)
/MCU/GRID_SYNC_2: J704.2, J705.2, J708.2, J709.2, U703.6 (GPIO4)
/MCU/GRID_WEST_RX: J704.3, U703.5 (GPIO3)
/MCU/GRID_WEST_TX: J703.2, U703.7 (GPIO5)
/MCU/LED_DATA_OUT: D901.3 (DIN), U704.27 (GPIO21)
/MCU/MAP_MODE: C757.1, R701.2, R736.2, U704.43 (GPIO38)
/MCU/RP_CLK: U703.20 (XIN), U704.21 (GPIO15)
/MCU/RP_INTERRUPT: U703.34 (GPIO22), U704.23 (GPIO17)
/MCU/RP_RUN: R729.2, U703.26 (RUN)
/MCU/RP_SPI0_CS: U703.28 (GPIO17), U704.12 (GPIO7)
/MCU/RP_SPI0_RX: U703.27 (GPIO16), U704.11 (GPIO6)
/MCU/RP_SPI0_SCK: U703.29 (GPIO18), U704.14 (GPIO9)
/MCU/RP_SPI0_TX: U703.30 (GPIO19), U704.13 (GPIO8)
/MCU/RP_SWCLK: U703.24 (SWCLK), U704.19 (GPIO14)
/MCU/RP_SWDIO: U703.25 (SWD), U704.18 (GPIO13)
/MCU/RP_UART0_RX: J702.3, U703.3 (GPIO1)
/MCU/RP_UART0_TX: J702.1, U703.2 (GPIO0)
/MCU/SPICLK: U704.33 (GPIO30), U705.6 (CLK)
/MCU/SPICS0: R734.2, U704.32 (GPIO29), U705.1 (~CS)
/MCU/SPID: U704.35 (GPIO32), U705.5 (DI(IO0))
/MCU/SPIHD: U704.30 (GPIO27), U705.7 (IO3)
/MCU/SPIQ: U704.34 (GPIO31), U705.2 (DO(IO1))
/MCU/SPIWP: U704.31 (GPIO28), U705.3 (IO2)
/MCU/TCK: J702.4, U704.44 (GPIO39)
/MCU/TDI: J702.8, U704.47 (GPIO41)
/MCU/TDO: J702.6, U704.45 (GPIO40)
/MCU/TMS: J702.2, U704.48 (GPIO42)
/MCU/U0RXD: J702.9, U704.50 (GPIO44)
/MCU/U0TXD: R733.2, U704.49 (GPIO43)
/MCU/USB_DN: J711.A7 (D-), J711.B7 (D-), TP713.1, U704.25 (GPIO19), U706.4, U706.6
/MCU/USB_DP: J711.A6 (D+), J711.B6 (D+), TP714.1, U704.26 (GPIO20), U706.1, U706.3
ESP_GPIO_1: U704.6 (GPIO1), U704.24 (GPIO18), U1001.3 (X)
ESP_GPIO_2: U704.7 (GPIO2), U1002.3 (X)
ESP_GPIO_3: U704.8 (GPIO3), U1002.9 (C)
ESP_GPIO_4: U704.9 (GPIO4), U1002.10 (B)
ESP_GPIO_5: U704.10 (GPIO5), U1002.11 (A)
ESP_GPIO_33: TP709.1, U704.38 (GPIO33)
ESP_GPIO_34: TP708.1, U704.39 (GPIO34)
ESP_GPIO_35: U704.40 (GPIO35), U1001.9 (C)
ESP_GPIO_36: U704.41 (GPIO36), U1001.10 (B)
ESP_GPIO_37: U704.42 (GPIO37), U1001.11 (A)
ESP_GPIO_47: TP706.1, U704.37 (GPIO47)
ESP_GPIO_48: TP707.1, U704.36 (GPIO48)
GND: C731.2, C732.2, C733.2, C734.2, C735.2, C736.2, C737.2, C738.2, C739.2, C740.2, C741.2, C742.2, C743.2, C744.2, C745.2, C746.2, C747.2, C748.2, C749.2, C750.2, C751.2, C752.2, C753.2, C754.2, C755.2, C756.2, C758.2, C759.2, C760.2, C761.1, C801.2, C901.1, C902.1, C903.1, C904.1, C905.1, C906.1, C907.1, C908.1, C909.1, C910.1, C911.1, C912.1, C1001.2, C1002.2, C1003.2, C1004.2, C1005.2, C1006.2, C1007.2, C1008.2, C1009.2, C1010.2, C1011.2, C1012.2, C1013.2, C1014.2, C1015.2, C1016.2, C1017.2, C1018.2, D901.2 (VSS), D902.2 (VSS), D903.2 (VSS), D904.2 (VSS), D905.2 (VSS), D906.2 (VSS), D907.2 (VSS), D908.2 (VSS), D909.2 (VSS), D910.2 (VSS), D911.2 (VSS), D912.2 (VSS), J701.2 (Ext), J702.5, J703.1, J704.4, J705.4, J706.1, J707.1, J708.4, J709.4, J710.1, J711.A1B12 (GND), J711.A12B1 (GND), J799.1, J799.2, R737.2, R738.2, R739.2, R1003.2, R1007.2, R1011.2, R1015.2, SW701.2 (B), SW702.1 (A), SW703.1 (A), TP705.1, TP710.1, TP711.1, U703.19 (TESTEN), U703.57 (GND), U704.57 (GND), U705.4 (GND), U706.2, U707.2 (GND), U801.3 (D4), U801.4 (D5), U801.5 (D6), U801.8 (GND), U801.10 (SI), U801.11 (D0), U801.13 (D2), U801.14 (D3), U801.15 (INH), U1001.6 (Inh), U1001.7 (VEE), U1001.8 (VSS), U1002.6 (Inh), U1002.7 (VEE), U1002.8 (VSS), UI1001.3, UI1002.3, UI1003.3, UI1004.3, UI1005.3, UI1006.3, UI1007.3, UI1008.3, UI1009.1, UI1009.2, UI1010.1, UI1010.2, UI1011.1, UI1011.2, UI1012.1, UI1012.2, Y701.2, Y701.4
unnamed: C749.1, L702.1, U704.2 (VDD3P3), U704.3 (VDD3P3)
unnamed: C760.1, L703.1, U707.1 (IN), U707.3 (EN)
unnamed: C759.1, J711.S1 (SHIELD)
unnamed: D901.1 (DOUT), D904.3 (DIN)
unnamed: D902.3 (DIN), D910.1 (DOUT)
unnamed: D902.1 (DOUT), D905.3 (DIN)
unnamed: D903.3 (DIN), D911.1 (DOUT)
unnamed: D903.1 (DOUT), D906.3 (DIN)
unnamed: D904.1 (DOUT), D907.3 (DIN)
unnamed: D905.1 (DOUT), D908.3 (DIN)
unnamed: D906.1 (DOUT), D909.3 (DIN)
unnamed: D907.1 (DOUT), D910.3 (DIN)
unnamed: D908.1 (DOUT), D911.3 (DIN)
unnamed: D909.1 (DOUT), D912.3 (DIN)
unnamed: C739.1, J701.1 (In), L701.1
unnamed: J702.7, R733.1
unnamed: J711.A5 (CC1), R738.1
unnamed: J711.B5 (CC2), R739.1
unnamed: J711.S2 (SHIELD), R737.1
unnamed: R1017.2, UI1001.1
unnamed: R1018.2, UI1002.1
unnamed: R1019.2, UI1003.1
unnamed: R1020.2, UI1004.1
unnamed: R1021.2, UI1005.1
unnamed: R1022.2, UI1006.1
unnamed: R1023.2, UI1007.1
unnamed: R1024.2, UI1008.1
unnamed: R1025.1, UI1009.4
unnamed: R1026.1, UI1010.3
unnamed: R1027.1, UI1011.4
unnamed: R1028.1, UI1012.3
unnamed: R736.1, SW701.1 (A)
unnamed: TP701.1, U703.15 (GPIO12)
unnamed: TP702.1, U703.16 (GPIO13)
unnamed: TP703.1, U703.17 (GPIO14)
unnamed: TP704.1, U703.18 (GPIO15)
unnamed: C750.1, U704.53 (XTAL_N), Y701.3
unnamed: C748.1, U704.54 (XTAL_P), Y701.1
unnamed: C1001.1, R1001.1, U1001.13 (X0)
unnamed: C1005.1, R1005.1, U1001.14 (X1)
unnamed: C1002.1, R1002.1, U1001.15 (X2)
unnamed: C1006.1, R1006.1, U1001.12 (X3)
unnamed: C1003.1, R1003.1, U1001.1 (X4)
unnamed: C1007.1, R1007.1, U1001.5 (X5)
unnamed: C1004.1, R1004.1, U1001.2 (X6)
unnamed: C1008.1, R1008.1, U1001.4 (X7)
unnamed: C1010.1, R1009.1, U1002.13 (X0)
unnamed: C1014.1, R1013.1, U1002.14 (X1)
unnamed: C1011.1, R1010.1, U1002.15 (X2)
unnamed: C1015.1, R1014.1, U1002.12 (X3)
unnamed: C1012.1, R1011.1, U1002.1 (X4)
unnamed: C1016.1, R1015.1, U1002.5 (X5)
unnamed: C1013.1, R1012.1, U1002.2 (X6)
unnamed: C1017.1, R1016.1, U1002.4 (X7)
VDD_SPI: C755.1, C756.1, R734.1, U704.29 (VDD_SPI), U705.8 (VCC)
